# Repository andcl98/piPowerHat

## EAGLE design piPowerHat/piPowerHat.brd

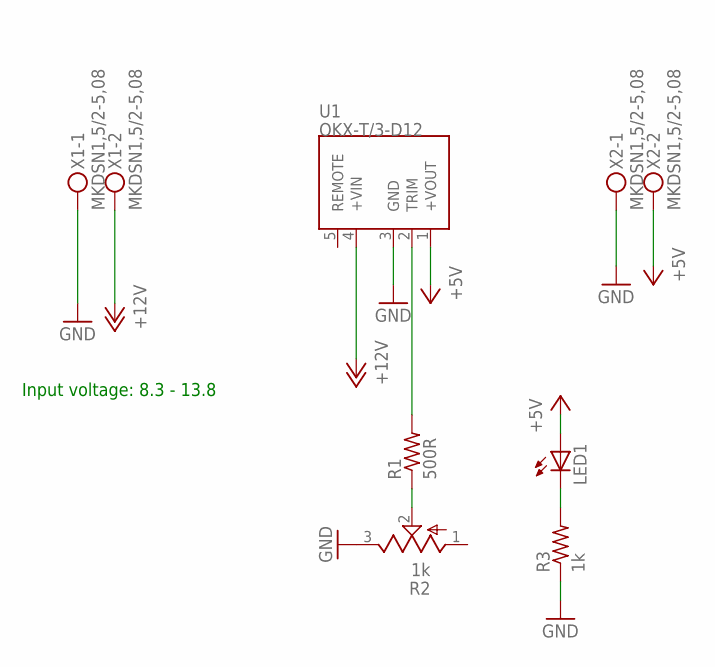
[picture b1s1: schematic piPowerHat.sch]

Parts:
LED1: LEDCHIP-LED0603; CHIP-LED0603
R1: 500R; R0603
R2: 1k; RTRIM3296W
R3: 1k; R0603
U1: OKX-T/3-D12
X1, X2: MKDSN1,5/2-5,08

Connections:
+5V: LED1.A, X2.2
+12V: U1.4 (+VIN), X1.2
GND: R2.3 (E), R3.1, U1.3 (GND), X1.1, X2.1
unnamed: R1.1, R2.2 (S)
unnamed: R1.2, U1.2 (TRIM)
unnamed: LED1.C, R3.2

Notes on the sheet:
Input voltage: 8.3 - 13.8

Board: 2 copper layers, 7 parts (0 on the bottom side), 6 nets, no tracks yet.

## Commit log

2021-04-18 first board
